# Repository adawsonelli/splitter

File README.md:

# splitter
KiCad project: a splitter board for a NI68PinConnector, which breaks out important pins, for the bike project

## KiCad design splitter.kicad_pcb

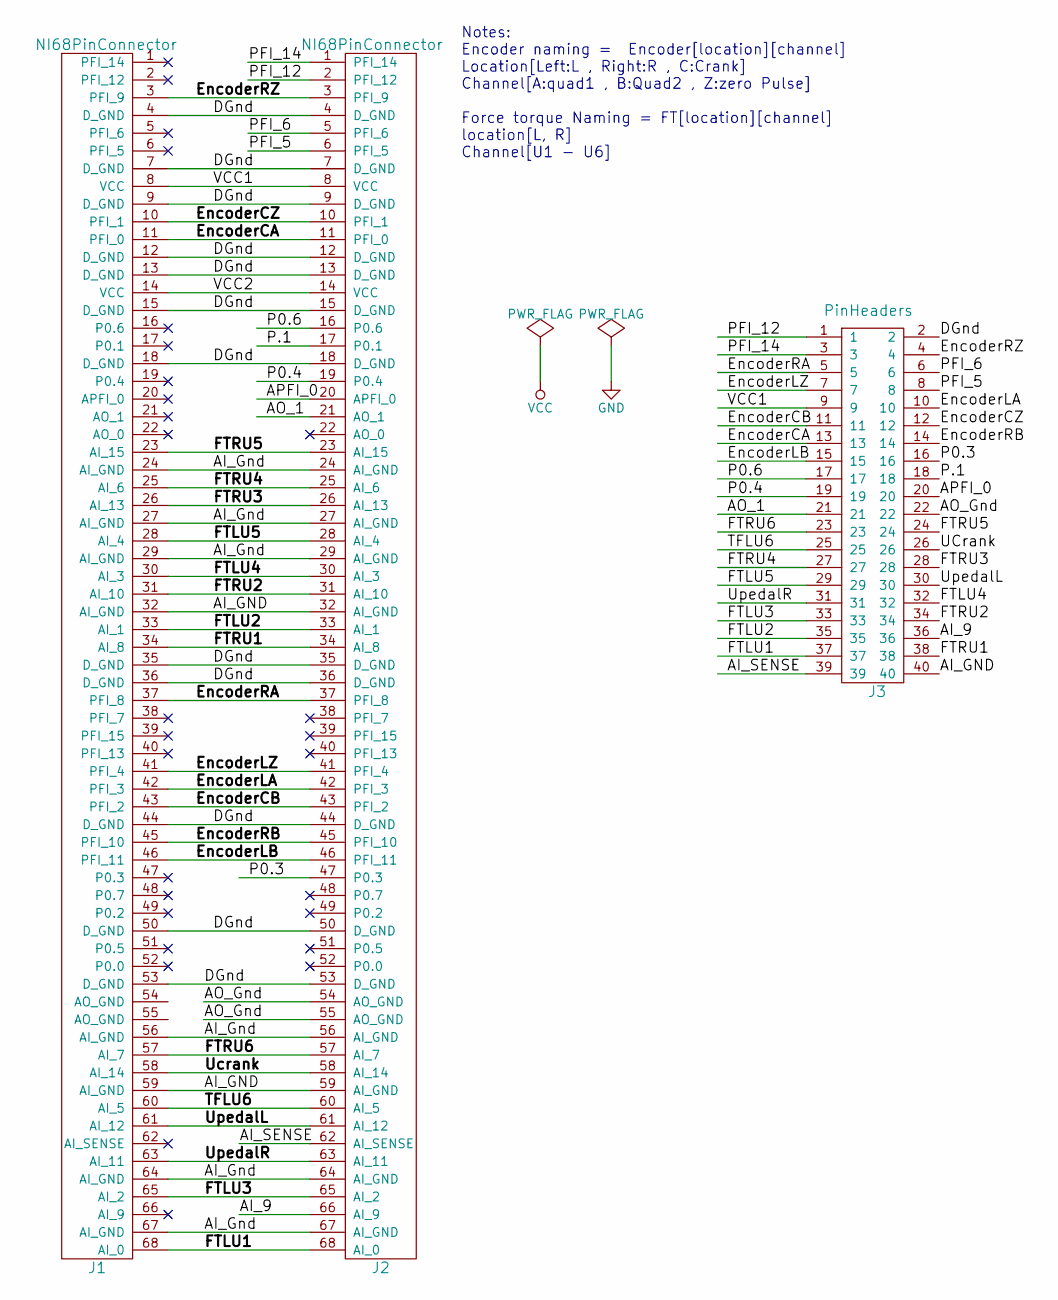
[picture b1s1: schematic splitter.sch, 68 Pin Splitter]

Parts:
J1: NI68PinConnector
J2: NI68PinConnector; NI68PinConnectorMirror
J3: PinHeaders; Pin_Header_Straight_2x20

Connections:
/AI_9: J2.66 (AI_9), J3.36
/AI_GND: J1.24 (AI_GND), J1.27 (AI_GND), J1.29 (AI_GND), J1.32 (AI_GND), J1.56 (AI_GND), J1.59 (AI_GND), J1.64 (AI_GND), J1.67 (AI_GND), J2.24 (AI_GND), J2.27 (AI_GND), J2.29 (AI_GND), J2.32 (AI_GND), J2.56 (AI_GND), J2.59 (AI_GND), J2.64 (AI_GND), J2.67 (AI_GND), J3.40
/AI_SENSE: J2.62 (AI_SENSE), J3.39
/AO_1: J2.21 (AO_1), J3.21
/AO_Gnd: J2.54 (AO_GND), J2.55 (AO_GND), J3.22
/APFI_0: J2.20 (APFI_0), J3.20
/DGnd: J1.4 (D_GND), J1.7 (D_GND), J1.9 (D_GND), J1.12 (D_GND), J1.13 (D_GND), J1.15 (D_GND), J1.18 (D_GND), J1.35 (D_GND), J1.36 (D_GND), J1.44 (D_GND), J1.50 (D_GND), J1.53 (D_GND), J2.4 (D_GND), J2.7 (D_GND), J2.9 (D_GND), J2.12 (D_GND), J2.13 (D_GND), J2.15 (D_GND), J2.18 (D_GND), J2.35 (D_GND), J2.36 (D_GND), J2.44 (D_GND), J2.50 (D_GND), J2.53 (D_GND), J3.2
/EncoderCA: J1.11 (PFI_0), J2.11 (PFI_0), J3.13
/EncoderCB: J1.43 (PFI_2), J2.43 (PFI_2), J3.11
/EncoderCZ: J1.10 (PFI_1), J2.10 (PFI_1), J3.12
/EncoderLA: J1.42 (PFI_3), J2.42 (PFI_3), J3.10
/EncoderLB: J1.46 (PFI_11), J2.46 (PFI_11), J3.15
/EncoderLZ: J1.41 (PFI_4), J2.41 (PFI_4), J3.7
/EncoderRA: J1.37 (PFI_8), J2.37 (PFI_8), J3.5
/EncoderRB: J1.45 (PFI_10), J2.45 (PFI_10), J3.14
/EncoderRZ: J1.3 (PFI_9), J2.3 (PFI_9), J3.4
/FTLU1: J1.68 (AI_0), J2.68 (AI_0), J3.37
/FTLU2: J1.33 (AI_1), J2.33 (AI_1), J3.35
/FTLU3: J1.65 (AI_2), J2.65 (AI_2), J3.33
/FTLU4: J1.30 (AI_3), J2.30 (AI_3), J3.32
/FTLU5: J1.28 (AI_4), J2.28 (AI_4), J3.29
/FTLU6: J1.60 (AI_5), J2.60 (AI_5), J3.25
/FTRU1: J1.34 (AI_8), J2.34 (AI_8), J3.38
/FTRU2: J1.31 (AI_10), J2.31 (AI_10), J3.34
/FTRU3: J1.26 (AI_13), J2.26 (AI_13), J3.28
/FTRU4: J1.25 (AI_6), J2.25 (AI_6), J3.27
/FTRU5: J1.23 (AI_15), J2.23 (AI_15), J3.24
/FTRU6: J1.57 (AI_7), J2.57 (AI_7), J3.23
/P0.1: J2.17 (P0.1), J3.18
/P0.3: J2.47 (P0.3), J3.16
/P0.4: J2.19 (P0.4), J3.19
/P0.6: J2.16 (P0.6), J3.17
/PFI_5: J2.6 (PFI_5), J3.8
/PFI_6: J2.5 (PFI_6), J3.6
/PFI_12: J2.2 (PFI_12), J3.1
/PFI_14: J2.1 (PFI_14), J3.3
/UCrank: J1.58 (AI_14), J2.58 (AI_14), J3.26
/UpedalL: J1.61 (AI_12), J2.61 (AI_12), J3.30
/UpedalR: J1.63 (AI_11), J2.63 (AI_11), J3.31
/VCC1: J1.8 (VCC), J2.8 (VCC), J3.9
/VCC2: J1.14 (VCC), J2.14 (VCC)

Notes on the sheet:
Notes: Encoder naming = Encoder[location][channel] Location[Left:L , Right:R , C:Crank] Channel[A:quad1 , B:Quad2 , Z:zero Pulse] Force torque Naming = FT[location][channel] location[L, R] Channel[U1 - U6]

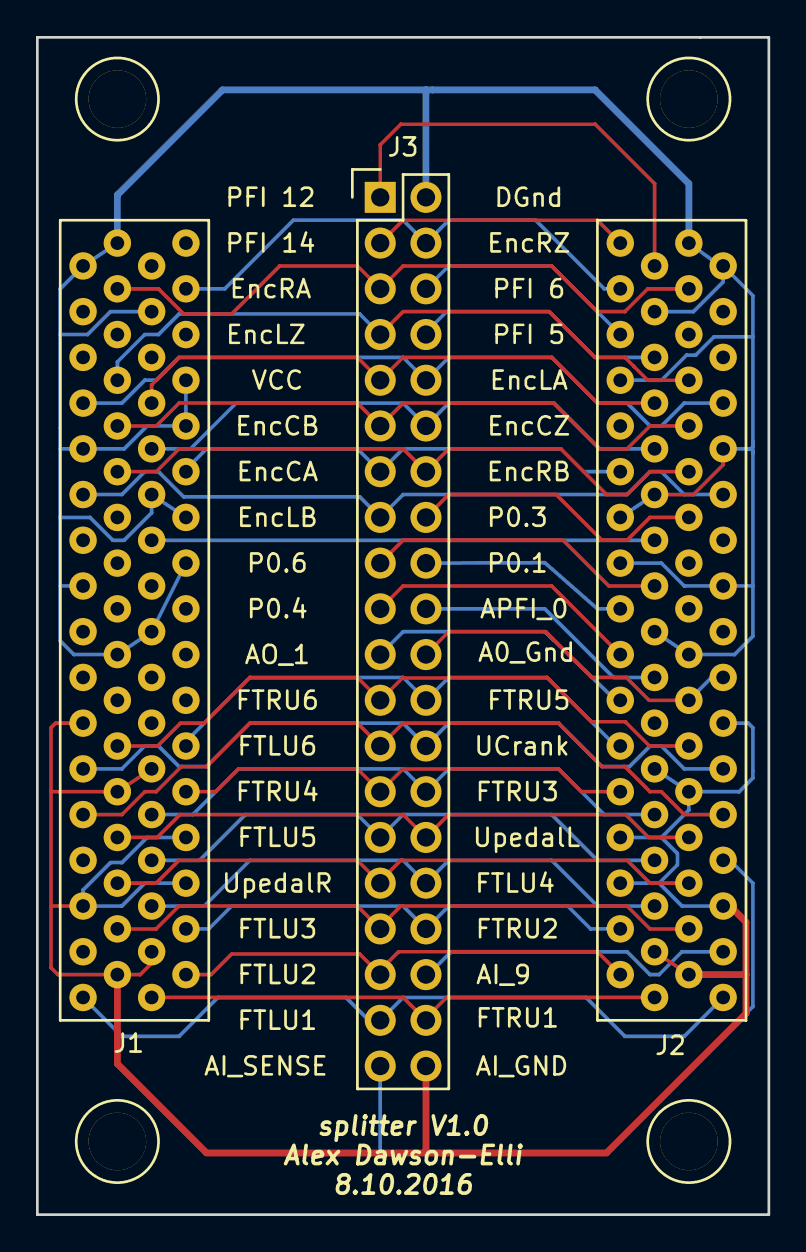
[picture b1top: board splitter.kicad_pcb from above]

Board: 2 copper layers, 40.6 x 65.4 mm, 3 parts (0 on the bottom side), 41 nets.

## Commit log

2016-07-28 first commit, board prototype 1 completed
2016-07-28 git ignore prevented my lib file from getting added!
2016-07-28 more withheld files
2016-08-09 added silk screen labels, post processed into gerber files
2016-08-10 updated standoff holes to be M3 clearance holes. Deleted stray traces that are located inside through holes, passed DRC.
